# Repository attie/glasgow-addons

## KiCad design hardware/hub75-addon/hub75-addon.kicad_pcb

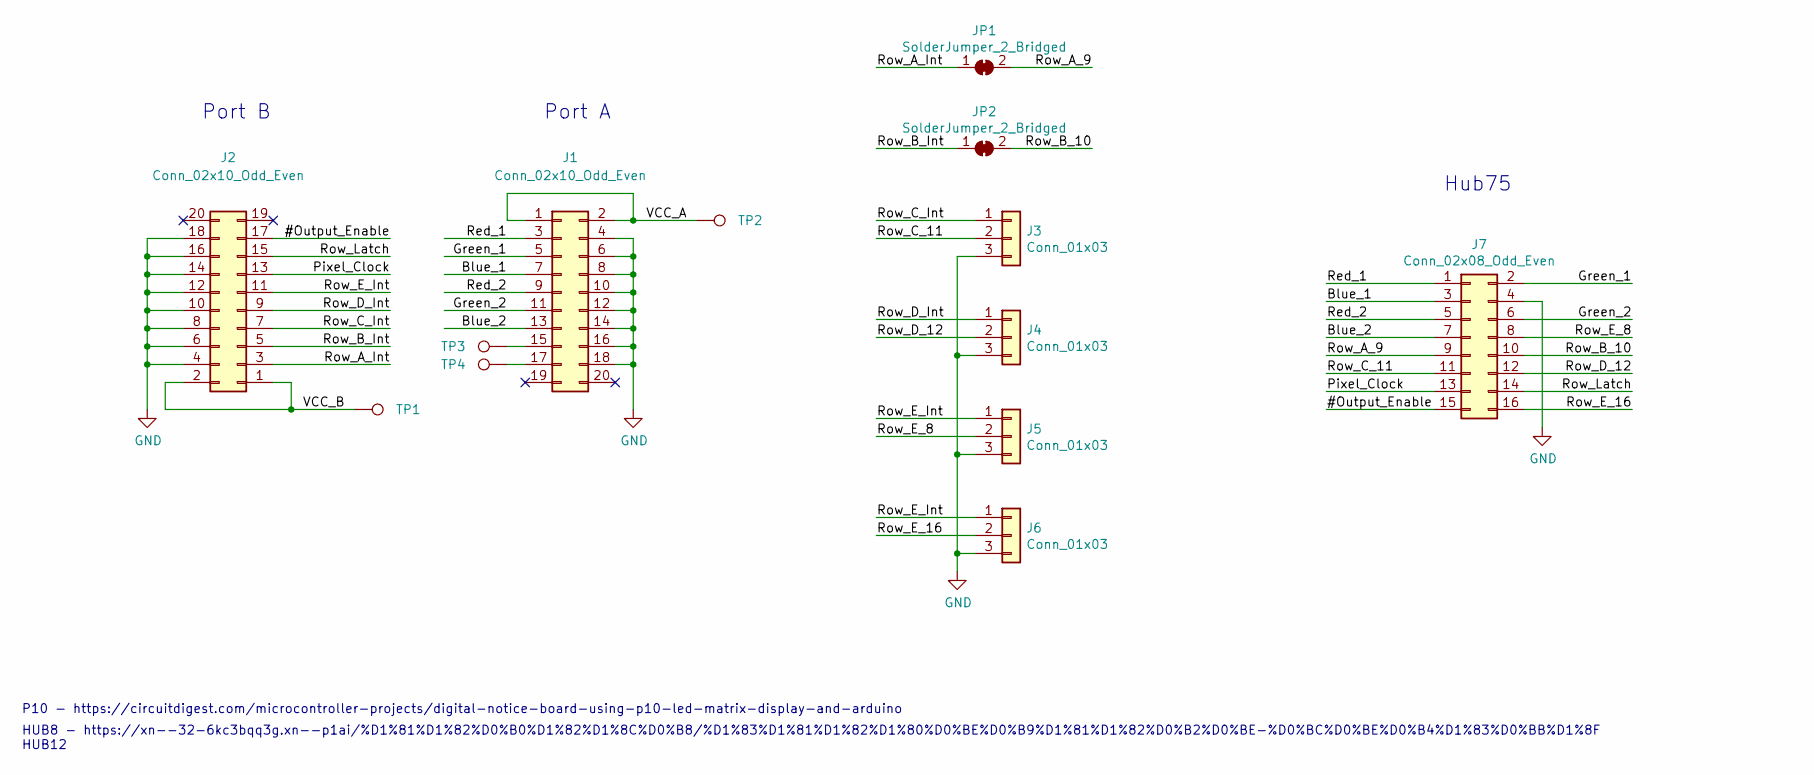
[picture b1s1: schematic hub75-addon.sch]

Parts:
J1, J2: Conn_02x10_Odd_Even; PinSocket_2x10_P2.54mm_Vertical
J3, J4, J5, J6: Conn_01x03; PinHeader_1x03_P2.54mm_Vertical
J7: Conn_02x08_Odd_Even; IDC-Header_2x08_P2.54mm_Vertical
JP1, JP2: SolderJumper_2_Bridged; J_NC_0603_30
TP1, TP2, TP3, TP4: TestPoint; Pin_Header_Straight_Round_1x01

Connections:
/#Output_Enable: J2.17, J7.15
/Blue_1: J1.7, J7.3
/Blue_2: J1.13, J7.7
/Green_1: J1.5, J7.2
/Green_2: J1.11, J7.6
/Pixel_Clock: J2.13, J7.13
/Red_1: J1.3, J7.1
/Red_2: J1.9, J7.5
/Row_A_9: J7.9, JP1.2 (B)
/Row_A_Int: J2.3, JP1.1 (A)
/Row_B_10: J7.10, JP2.2 (B)
/Row_B_Int: J2.5, JP2.1 (A)
/Row_C_11: J3.2, J7.11
/Row_C_Int: J2.7, J3.1
/Row_D_12: J4.2, J7.12
/Row_D_Int: J2.9, J4.1
/Row_E_8: J5.2, J7.8
/Row_E_16: J6.2, J7.16
/Row_E_Int: J2.11, J5.1, J6.1
/Row_Latch: J2.15, J7.14
/VCC_A: J1.1, J1.2, TP2.1
/VCC_B: J2.1, J2.2, TP1.1
GND: J1.4, J1.6, J1.8, J1.10, J1.12, J1.14, J1.16, J1.18, J2.4, J2.6, J2.8, J2.10, J2.12, J2.14, J2.16, J2.18, J3.3, J4.3, J5.3, J6.3, J7.4
unnamed: J1.15, TP3.1
unnamed: J1.17, TP4.1

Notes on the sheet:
Port A
Port B
P10 - https://circuitdigest.com/microcontroller-projects/digital-notice-board-using-p10-led-matrix-display-and-arduino
HUB8 - https://xn--32-6kc3bqq3g.xn--p1ai/%D1%81%D1%82%D0%B0%D1%82%D1%8C%D0%B8/%D1%83%D1%81%D1%82%D1%80%D0%BE%D0%B9%D1%81%D1%82%D0%B2%D0%BE-%D0%BC%D0%BE%D0%B4%D1%83%D0%BB%D1%8F HUB12
Hub75

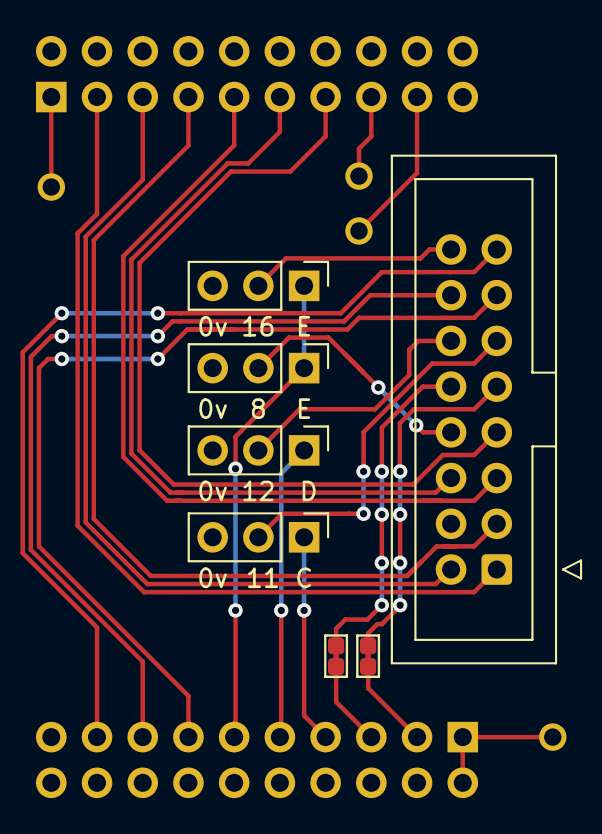
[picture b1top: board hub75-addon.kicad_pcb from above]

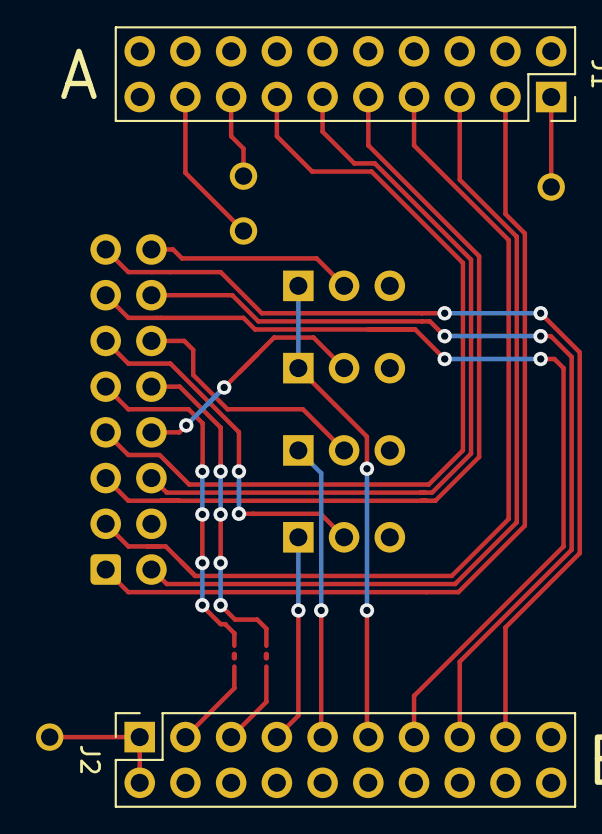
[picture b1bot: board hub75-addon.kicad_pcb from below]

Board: 2 copper layers, 13 parts (2 on the bottom side), 25 nets.

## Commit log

2021-04-08 WIP: hub75-addon: start schematic & layout
